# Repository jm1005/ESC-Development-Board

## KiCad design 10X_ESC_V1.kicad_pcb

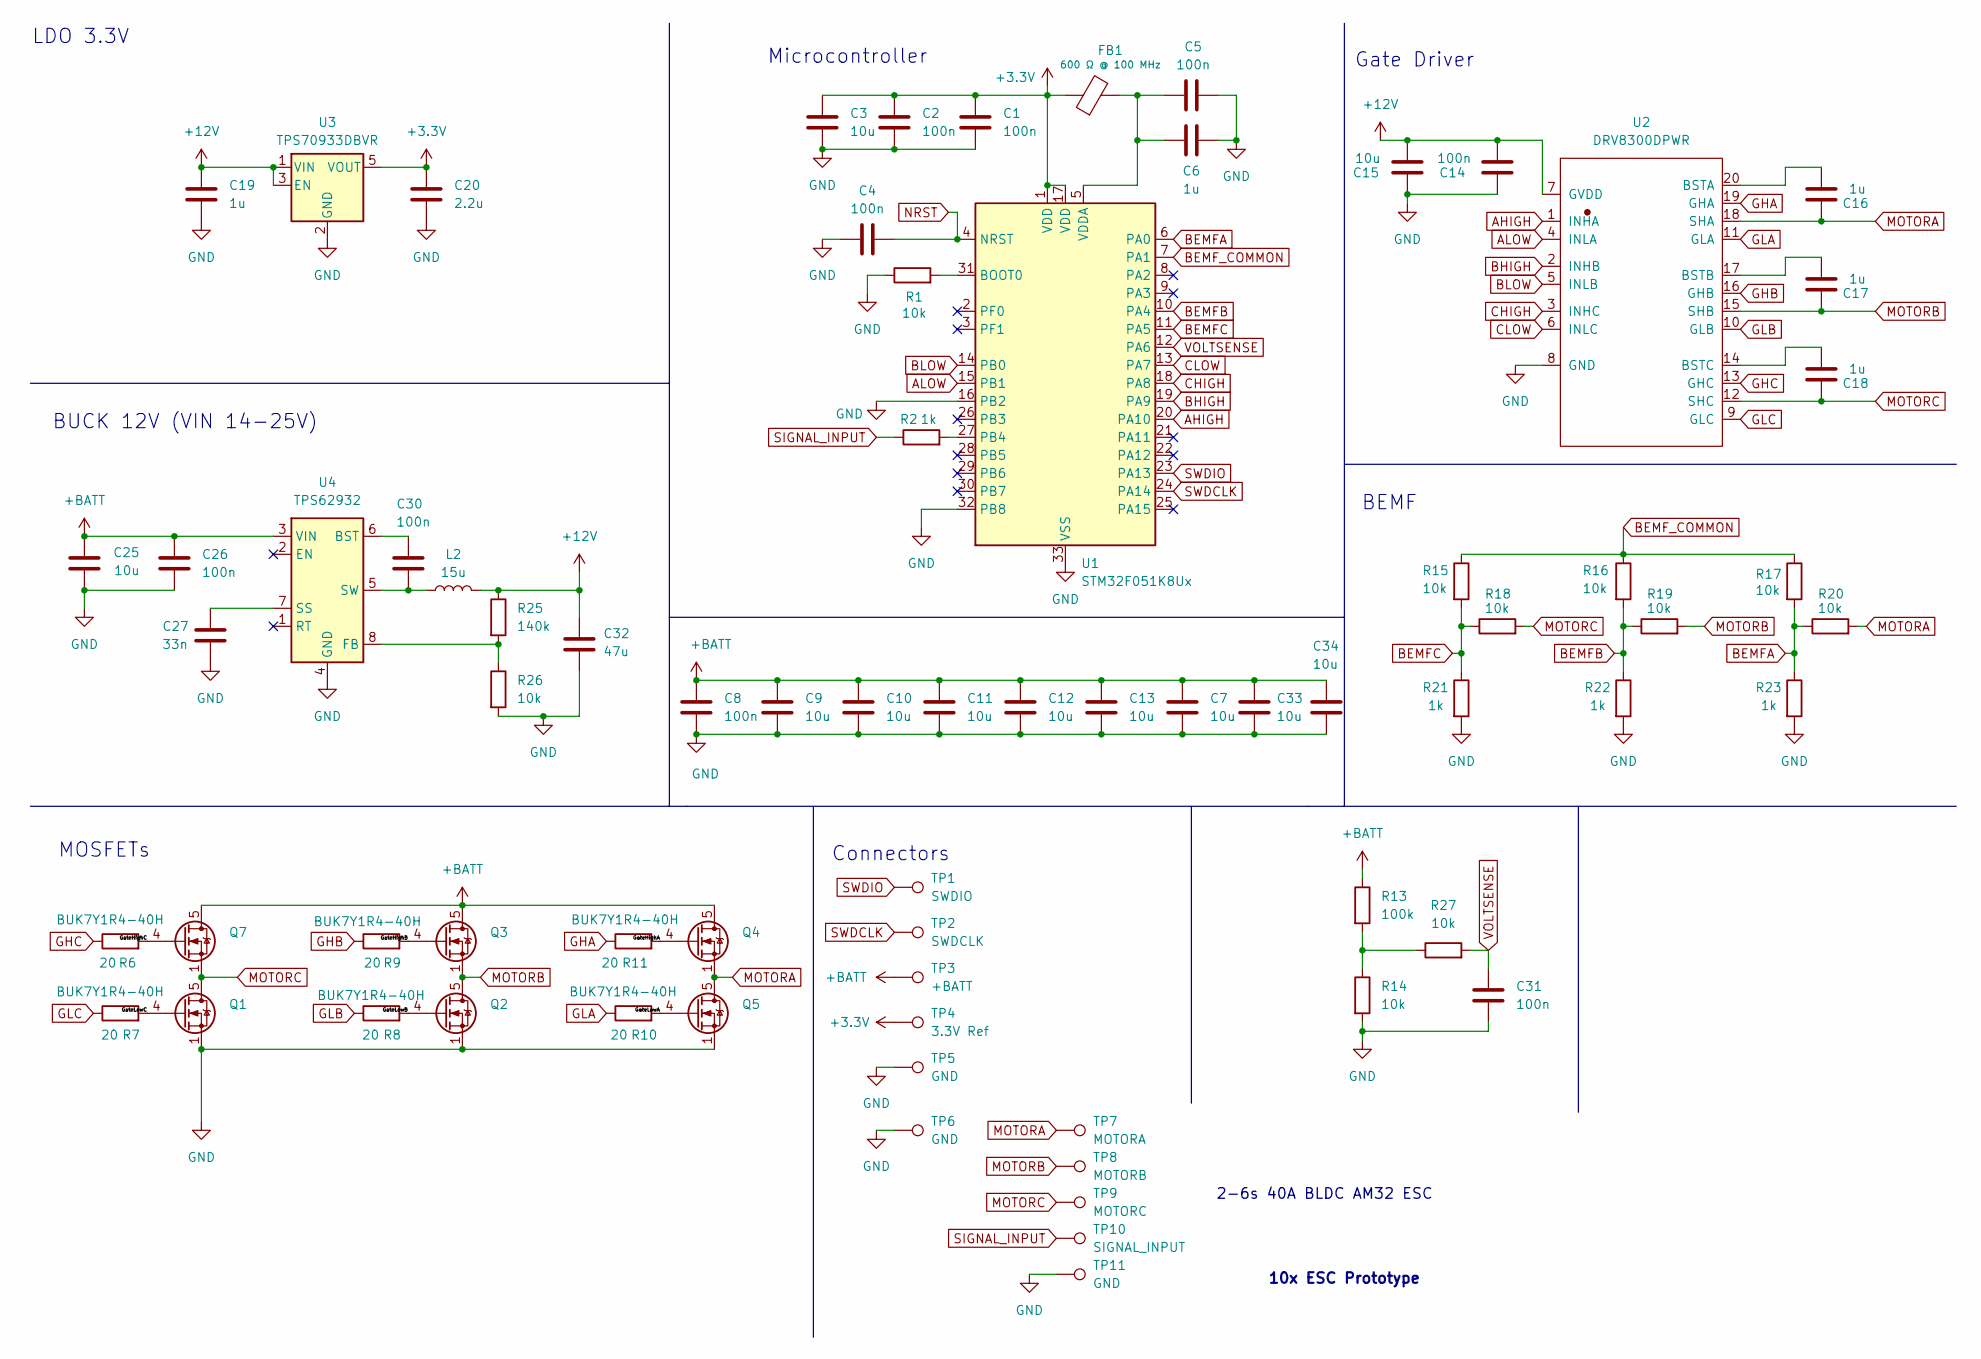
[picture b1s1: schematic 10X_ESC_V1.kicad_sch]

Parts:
C1, C2, C4, C5, C14, C30, C31: 100n; C_0402_1005Metric; Manufacturer Part Number CA0522618; LCSC Part # C307331
C3, C15: 10u; C_0603_1608Metric; LCSC Part # C96446
C6: 1u; C_0402_1005Metric; LCSC Part # C52923
C7, C9, C10, C11, C12, C13, C33, C34: 10u; C_1210_3225Metric; LCSC Part # C53084452
C8: 100n; C_1210_3225Metric; LCSC Part # C2179722
C16, C17, C18: 1u; C_0603_1608Metric; LCSC Part # C15849
C19: 1u; C_0603_1608Metric
C20: 2.2u; C_0603_1608Metric
C25: 10u; C_0805_2012Metric; LCSC Part # C440198
C26: 100n; C_0603_1608Metric; LCSC Part # C14663
C27: 33n; C_0402_1005Metric; LCSC Part # C106862
C32: 47u; C_1210_3225Metric; LCSC Part # C77101
FB1: 600 Ω @ 100 MHz; L_0603_1608Metric; LCSC Part # C85833
L2: 15u; L_KOHERelec_MDA7030; LCSC Part # C2847486
Q1, Q2, Q3, Q4, Q5, Q7: BUK7Y1R4-40H; LFPAK56; LCSC Part # C6423721
R1, R14, R15, R16, R17, R18, R19, R20, R26, R27: 10k; R_0402_1005Metric; LCSC Part # C25744
R2, R21, R22, R23: 1k; R_0402_1005Metric; LCSC Part # C11702
R6, R7, R8, R9, R10, R11: 20; R_0402_1005Metric; LCSC Part # C25089
R13: 100k; R_0402_1005Metric; LCSC Part # C25741
R25: 140k; R_0402_1005Metric; LCSC Part # C114151
TP1: SWDIO; TestPoint_Pad_D1.0mm
TP2: SWDCLK; TestPoint_Pad_D1.0mm
TP3: +BATT; TestPoint_Pad_3.0x3.0mm
TP4: 3.3V Ref; TestPoint_Pad_D1.0mm
TP5: GND; TestPoint_Pad_D1.0mm
TP6: GND; TestPoint_Pad_3.0x3.0mm
TP7: MOTORA; TestPoint_Pad_2.5x2.5mm
TP8: MOTORB; TestPoint_Pad_2.5x2.5mm
TP9: MOTORC; TestPoint_Pad_2.5x2.5mm
TP10: SIGNAL_INPUT; TestPoint_Pad_1.5x1.5mm
TP11: GND; TestPoint_Pad_1.5x1.5mm
U1: STM32F051K8Ux; QFN-32-1EP_5x5mm_P0.5mm_EP3.45x3.45mm; LCSC Part # C72339
U2: DRV8300DPWR; TSSOP-20_L6.5-W4.4-P0.65-LS6.4-BL; LCSC Part # C3036056
U3: TPS70933DBVR; SOT-23-5
U4: TPS62932; SOT-583-8; LCSC Part # C3032935

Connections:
+3.3V: C1.1, C2.1, C3.1, C20.1, FB1.1, TP4.1 (1_1), U1.1 (VDD), U1.17 (VDD), U3.5 (VOUT)
+12V: C14.2, C15.2, C19.1, C32.1, L2.2, R25.1, U2.7 (GVDD), U3.1 (VIN), U3.3 (EN)
+BATT: C7.1, C8.1, C9.1, C10.1, C11.1, C12.1, C13.1, C25.1, C26.1, C33.1, C34.1, Q3.5 (D), Q4.5 (D), Q7.5 (D), R13.1, TP3.1 (1_1), U4.3 (VIN)
/GateHighA: Q4.4 (G), R11.2
/GateHighB: Q3.4 (G), R9.2
/GateHighC: Q7.4 (G), R6.2
/GateLowA: Q5.4 (G), R10.2
/GateLowB: Q2.4 (G), R8.2
/GateLowC: Q1.4 (G), R7.2
AHIGH: U1.20 (PA10), U2.1 (INHA)
ALOW: U1.15 (PB1), U2.4 (INLA)
BEMFA: R17.2, R20.1, R23.1, U1.6 (PA0)
BEMFB: R16.2, R19.1, R22.1, U1.10 (PA4)
BEMFC: R15.2, R18.1, R21.1, U1.11 (PA5)
BEMF_COMMON: R15.1, R16.1, R17.1, U1.7 (PA1)
BHIGH: U1.19 (PA9), U2.2 (INHB)
BLOW: U1.14 (PB0), U2.5 (INLB)
CHIGH: U1.18 (PA8), U2.3 (INHC)
CLOW: U1.13 (PA7), U2.6 (INLC)
GHA: R11.1, U2.19 (GHA)
GHB: R9.1, U2.16 (GHB)
GHC: R6.1, U2.13 (GHC)
GLA: R10.1, U2.11 (GLA)
GLB: R8.1, U2.10 (GLB)
GLC: R7.1, U2.9 (GLC)
GND: C1.2, C2.2, C3.2, C4.1, C5.2, C6.2, C7.2, C8.2, C9.2, C10.2, C11.2, C12.2, C13.2, C14.1, C15.1, C19.2, C20.2, C25.2, C26.2, C27.2, C31.2, C32.2, C33.2, C34.2, Q1.1 (S), Q1.2 (S), Q1.3 (S), Q2.1 (S), Q2.2 (S), Q2.3 (S), Q5.1 (S), Q5.2 (S), Q5.3 (S), R1.1, R14.2, R21.2, R22.2, R23.2, R26.2, TP5.1 (1_1), TP6.1 (1_1), TP11.1 (1_1), U1.16 (PB2), U1.32 (PB8), U1.33 (VSS), U2.8 (GND), U3.2 (GND), U4.4 (GND)
MOTORA: C16.1, Q4.1 (S), Q4.2 (S), Q4.3 (S), Q5.5 (D), R20.2, TP7.1 (1_1), U2.18 (SHA)
MOTORB: C17.1, Q2.5 (D), Q3.1 (S), Q3.2 (S), Q3.3 (S), R19.2, TP8.1 (1_1), U2.15 (SHB)
MOTORC: C18.1, Q1.5 (D), Q7.1 (S), Q7.2 (S), Q7.3 (S), R18.2, TP9.1 (1_1), U2.12 (SHC)
NRST: C4.2, U1.4 (NRST)
unnamed: R13.2, R14.1, R27.1
unnamed: R1.2, U1.31 (BOOT0)
unnamed: R2.2, U1.27 (PB4)
unnamed: C5.1, C6.1, FB1.2, U1.5 (VDDA)
unnamed: C16.2, U2.20 (BSTA)
unnamed: C17.2, U2.17 (BSTB)
unnamed: C18.2, U2.14 (BSTC)
unnamed: C30.1, U4.6 (BST)
unnamed: R25.2, R26.1, U4.8 (FB)
unnamed: C27.1, U4.7 (SS)
unnamed: C30.2, L2.1, U4.5 (SW)
SIGNAL_INPUT: R2.1, TP10.1 (1_1)
SWDCLK: TP2.1 (1_1), U1.24 (PA14)
SWDIO: TP1.1 (1_1), U1.23 (PA13)
VOLTSENSE: C31.1, R27.2, U1.12 (PA6)

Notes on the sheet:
2-6s 40A BLDC AM32 ESC
BEMF
MOSFETs
LDO 3.3V
Gate Driver
10x ESC Prototype
BUCK 12V (VIN 14-25V)
Microcontroller
Connectors

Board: 4 copper layers, 73 parts (25 on the bottom side), 45 nets, no tracks yet.
